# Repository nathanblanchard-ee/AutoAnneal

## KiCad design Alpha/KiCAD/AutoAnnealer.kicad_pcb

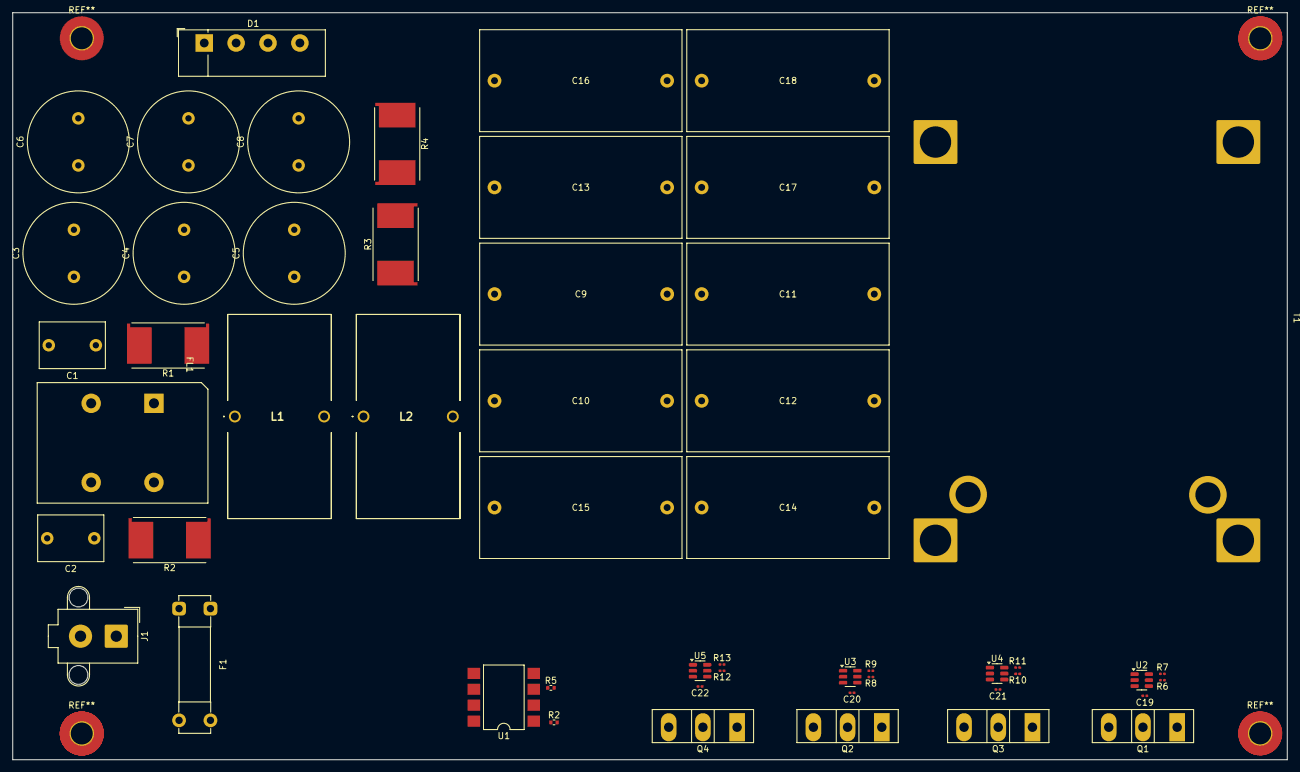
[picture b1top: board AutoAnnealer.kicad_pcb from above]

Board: 2 copper layers, 203.0 x 119.0 mm, 52 parts (0 on the bottom side), 26 nets, no tracks yet.

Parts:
C1, C2: C; C_Rect_L10.3mm_W7.2mm_P7.50mm_MKS4
C3, C4, C5, C6, C7, C8: C_Polarized; C_Radial_D16.0mm_H25.0mm_P7.50mm
C9, C10, C11, C12, C13, C14, C15, C16, C17, C18: C; C_Rect_L32.0mm_W16.0mm_P27.50mm
C19, C20, C21, C22: C; C_0201_0603Metric
D1: KBU6G; Diode_Bridge_Vishay_KBU
F1: Fuse; Fuseholder_Clip-5x20mm_Bel_FC-203-22_Lateral_P17.80x5.00mm_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
FL1: Choke_CommonMode_PulseElectronics_PH9455x356NL; L_CommonMode_PulseElectronics_PH9455xxx6NL_2
J1: AC-IN; Molex_Mega-Fit_76829-0002_2x01_P5.70mm_Vertical
L1, L2: L_Ferrite; 2318VRC
Q1, Q2, Q3, Q4: Q_NMOS_DGS; TO-247-3_Vertical
R1: 300k; R_Shunt_Vishay_WSR2_WSR3_KelvinConnection
R2, R4: R; R_Shunt_Vishay_WSR2_WSR3_KelvinConnection
R2#2, R5: R; R_0402_1005Metric
R3: 220K; R_Shunt_Vishay_WSR2_WSR3_KelvinConnection
R6, R7, R8, R9, R10, R11, R12, R13: R; R_0201_0603Metric
T1: WorkTransformer
U1: LTV-827S; SMDIP-8_W9.53mm
U2, U3, U4, U5: 1EDN7550B; SOT-23-6

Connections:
/AnnealerOutput/Driver1_Ref: C9.1, C10.1, C11.1, C12.1, C13.1, C14.1, C15.1, C16.1, C17.1, C18.1, L1.1, Q1.1 (D), Q3.1 (D), R2#2.1, T1.1
/AnnealerOutput/Driver2_Ref: C9.2, C10.2, C11.2, C12.2, C13.2, C14.2, C15.2, C16.2, C17.2, C18.2, L2.2, Q2.1 (D), Q4.1 (D), R5.1, T1.2
/AnnealerOutput/Driver_1-1: Q3.2 (G), R10.2, R11.2
/AnnealerOutput/Driver_1-2: Q1.2 (G), R6.2, R7.2
/AnnealerOutput/Driver_2-1: Q2.2 (G), R8.2, R9.2
/AnnealerOutput/HVDC: C3.1, C4.1, C5.1, C6.1, C7.1, C8.1, D1.1 (+), L1.2, L2.1, R3.1, R4.1
/Transformer_Driver/Driver2-2: R12.2, R13.2
GND: C3.2, C4.2, C5.2, C6.2, C7.2, C8.2, C19.2, C20.2, C21.2, C22.2, D1.4 (-), Q1.3 (S), Q2.3 (S), Q3.3 (S), Q4.3 (S), R3.2, R4.2, T1.3 (Core), U1.2, U1.4, U2.2 (GND), U3.2 (GND), U4.2 (GND), U5.2 (GND)
LINE: C1.1, F1.1, FL1.1, J1.1, R1.1
NEUTRAL: C1.2, FL1.2, R1.2
unnamed: C2.1, D1.3, FL1.4, R2.1
unnamed: C2.2, D1.2, FL1.3, R2.2
unnamed: R2#2.2, U1.1
unnamed: R5.2, U1.3
unnamed: R7.1, U2.6 (OUT_SNK)
unnamed: R6.1, U2.5 (OUT_SRC)
unnamed: C19.1, U2.4 (VDD)
unnamed: R9.1, U3.6 (OUT_SNK)
unnamed: R8.1, U3.5 (OUT_SRC)
unnamed: C20.1, U3.4 (VDD)
unnamed: R11.1, U4.6 (OUT_SNK)
unnamed: R10.1, U4.5 (OUT_SRC)
unnamed: C21.1, U4.4 (VDD)
unnamed: R13.1, U5.6 (OUT_SNK)
unnamed: R12.1, U5.5 (OUT_SRC)
unnamed: C22.1, U5.4 (VDD)

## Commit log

2025-09-10 Add LTSpice files
2025-09-10 Add STEP files
